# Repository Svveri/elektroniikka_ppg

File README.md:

# elektroniikka_ppg
Elektroniikan sovellusprojektissa suunnittelemme fotopletysmografia periaatteella sydämmensykettä seuraavan laitteen. Tässä repositoriossa säilytämme siihen liittyvät koodit.

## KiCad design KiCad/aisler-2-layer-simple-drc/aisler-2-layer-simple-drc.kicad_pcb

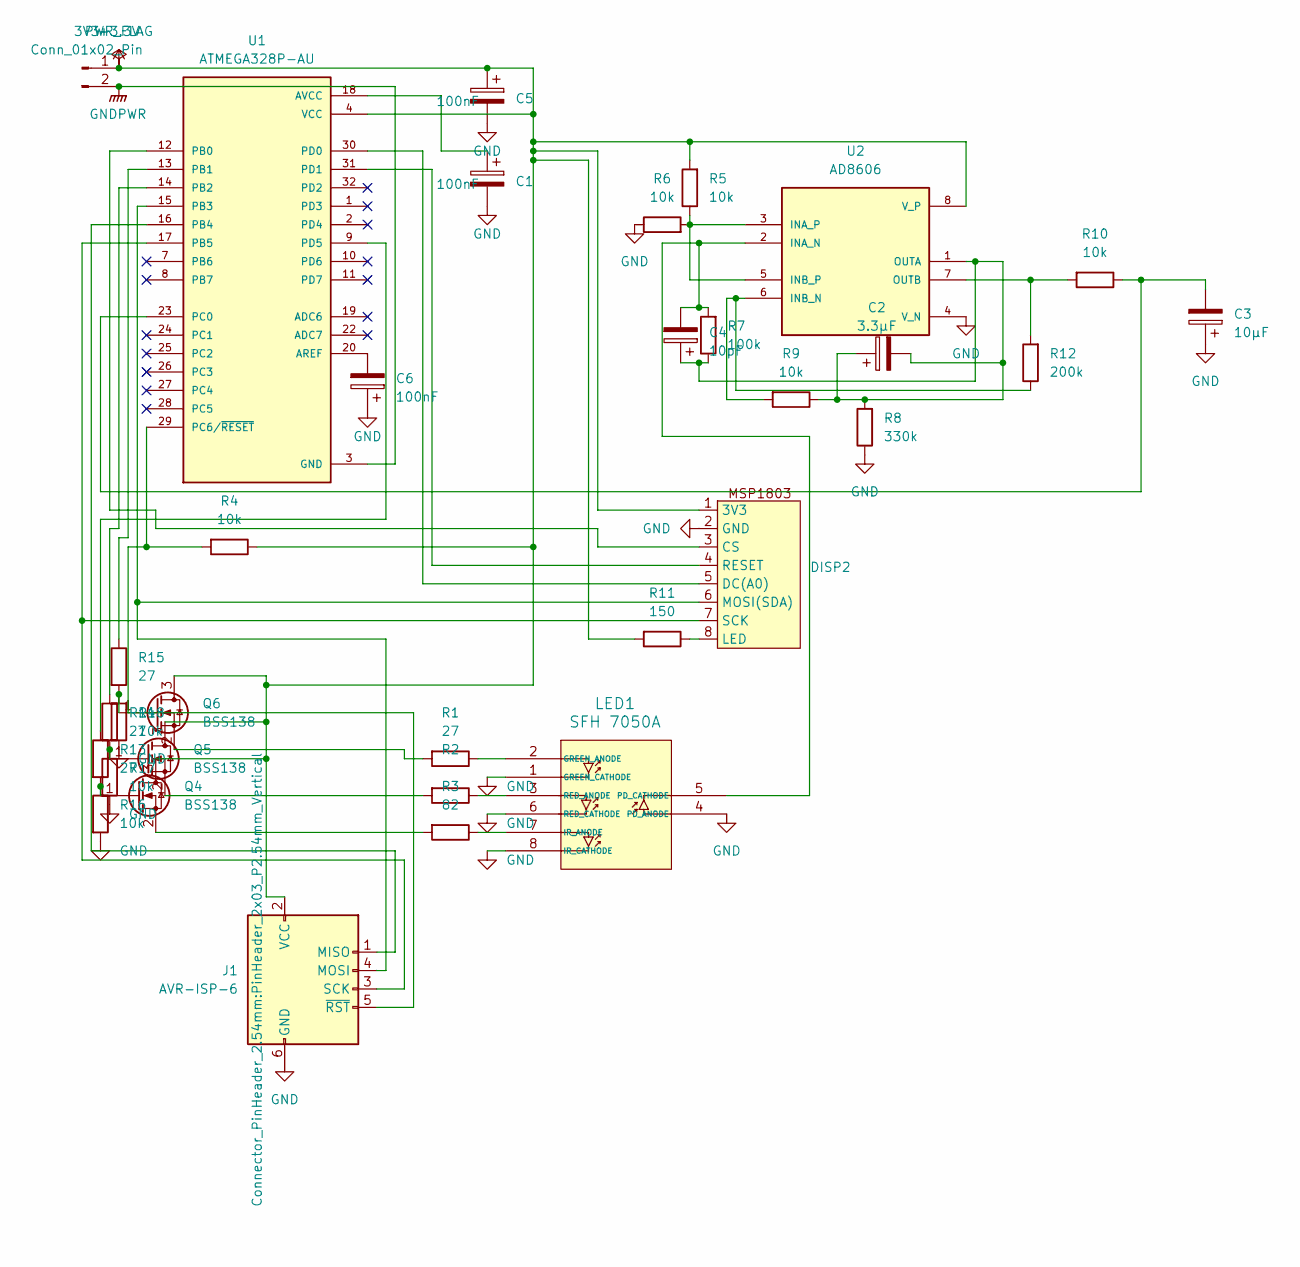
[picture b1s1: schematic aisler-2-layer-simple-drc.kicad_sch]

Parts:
3V3: Conn_01x02_Pin; PinHeader_1x02_P2.54mm_Vertical
C1, C5, C6: 100nF; C_0805_2012Metric
C2: 3.3µF; C_0805_2012Metric
C3: 10µF; C_0805_2012Metric
C4: 10pF; C_0805_2012Metric
DISP2: PinHeader_1x08_P2.54mm_Vertical
J1: AVR-ISP-6; PinHeader_2x03_P2.54mm_Vertical
LED1: SFH 7050A; SFH 7050A_OSM
Q4, Q5, Q6: BSS138; SOT-23
R1, R13, R14, R15: 27; R_0805_2012Metric
R2: 56; R_0805_2012Metric
R3: 82; R_0805_2012Metric
R4, R5, R6, R9, R10, R16, R17, R18: 10k; R_0805_2012Metric
R7: 100k; R_0805_2012Metric
R8: 330k; R_0805_2012Metric
R11: 150; R_0805_2012Metric
R12: 200k; R_0805_2012Metric
U1: ATMEGA328P-AU; TQFP-32_7x7mm_P0.8mm; PARTREV 8271A
U2: AD8606; SOIC-8_3.9x4.9mm_P1.27mm; PARTREV Rev. O

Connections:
+3.3V: 3V3.1, C5.1, DISP2.1 (3V3), J1.2 (VCC), Q4.3 (D), Q5.3 (D), Q6.3 (D), R4.1, R5.2, R11.2, U1.4 (VCC), U1.6 (VCC), U2.8 (V_P)
unnamed: DISP2.3 (CS), U1.12 (PB0)
unnamed: DISP2.5 (DC(A0)), U1.30 (PD0)
unnamed: DISP2.8 (LED), R11.1
unnamed: DISP2.6 (MOSI(SDA)), J1.4 (MOSI), U1.15 (PB3)
unnamed: DISP2.4 (RESET), U1.31 (PD1)
unnamed: DISP2.7 (SCK), J1.3 (SCK), U1.17 (PB5)
unnamed: J1.1 (MISO), U1.16 (PB4)
unnamed: J1.5 (~RST), R4.2, U1.29 (PC6/~RESET)
unnamed: LED1.2 (GREEN_ANODE), R1.1
unnamed: LED1.7 (IR_ANODE), R3.1
unnamed: C4.2, LED1.5 (PD_CATHODE), R7.2, U2.2 (INA_N)
unnamed: LED1.3 (RED_ANODE), R2.1
unnamed: Q4.1 (G), R13.2, R16.1
unnamed: Q4.2 (S), R3.2
unnamed: Q5.1 (G), R14.2, R17.1
unnamed: Q5.2 (S), R2.2
unnamed: Q6.1 (G), R15.2, R18.1
unnamed: Q6.2 (S), R1.2
unnamed: C6.2, U1.20 (AREF)
unnamed: C1.1, U1.18 (AVCC)
unnamed: R15.1, U1.13 (PB1)
unnamed: R14.1, U1.14 (PB2)
unnamed: C3.2, R10.1, U1.23 (PC0)
unnamed: R13.1, U1.9 (PD5)
unnamed: R5.1, R6.2, U2.3 (INA_P), U2.5 (INB_P)
unnamed: R9.2, R12.1, U2.6 (INB_N)
unnamed: C2.1, C2.2, C4.1, R7.1, R8.2, R9.1, U2.1 (OUTA)
unnamed: R10.2, R12.2, U2.7 (OUTB)

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
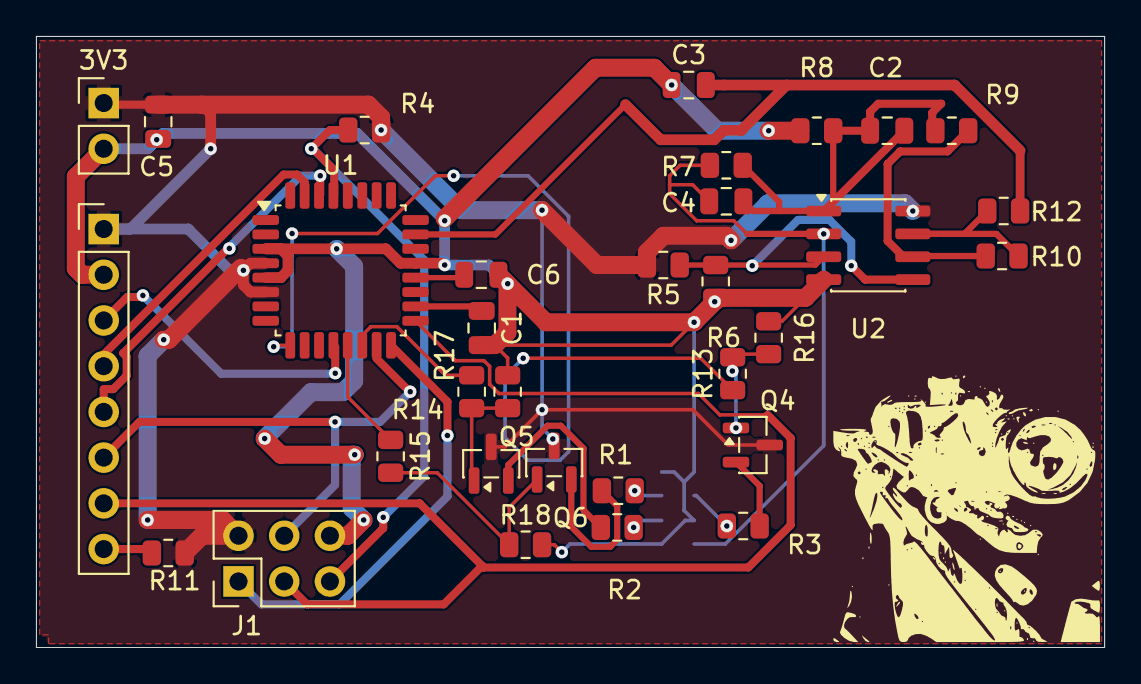
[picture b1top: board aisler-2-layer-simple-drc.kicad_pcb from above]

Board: 2 copper layers, 59.3 x 33.9 mm, 33 parts (1 on the bottom side), 30 nets.

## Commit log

2026-04-01 Poistin .history ja ignoresin sen
2026-04-01 KiCad tiedostot
2026-04-01 Lisätty kooditiedostojen alut kansioon nimeltä koodi. Tiedostoissa ei vielä mitään koodia luotuna tässä vaiheessa
2026-04-02 Validoitu signaalin mittaus DFROBOT_heartrate kirjastolla. Eli A0 pinniin kytkettynä, nappia paineltaessa kykenee mittaamaan signaalin ja printtaamaan sen serial monitorille.
2026-04-07 Added new code (monitor DEMO)
2026-04-08 Lisäsin heart_rate kansioon monitoria varten header ja cpp tiedoston, joilla päästään käsiksi sykkeen luomaan aaltoihin (tällä hetkellä vielä on demo meinaan ei ole sykemittaria. Hyvin kommentoitu ja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
2026-04-09 Yhdistetty RR-intervalli metodia käyttäen toimiva sykkeen mittaus. Tämä koodi toimi hienosti napilla sykettä simuloiden
2026-04-13 Tässä vaiheessa muutettu näytölle menevän muuttujan merkitys, ottaa nyt vastaan napin painalluksen sykkeen eikä simuloida sykettä ohjelmallisesti. Muutettu funktiota ottamaan vastaan muuttuja lastBPM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
2026-04-13 Edelleen toimii samanlailla kuin edellinen, vähän siistitty koodia yms. ei mitään toiminnallista muutosta
2026-04-14 Poistettu turha funktio monitor.cpp, tässä kohtaa koodi edelleen kirjoittaa bpm näytölle, mutta käyrä ei piirry oikein
2026-04-14 Fixed problem with button not showing up on screen, big delay on updated bpm etc.
2026-04-15 Muutettu koodin rr intervalliin liittyvä osa omaksi funktioksi, tässä hetkessä ei koodi vielä toimi kunnolla näytön kanssa
2026-04-16 Siirretty omiin funktioihin asioita ino tiedostosta yms, tässä vaiheessa koodi hajoaa kun syke nousee liian korkeaksi.
2026-04-16 Tässä branchissa testailen vaihtoehtoisia koodeja. Löysin toisen kirjaston nimeltä PulseSensorPlayground, ja sen metodit vaikuttaa toimivan paljon paremmin kuin aikaisemman kirjaston ja itse tekemän 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
2026-04-16 Muutettu koodia radikaalisti, vaihdettu kirjastoa mitä käytetään (PulseSensorPlayground) ja koodi toimii toistaiseksi oikein hyvin. Näytölle piirtyy bpm ja signaalin käyrä oikein hyvin
2026-04-16 Poistettu source.cpp ja source.h toistaiseksi, uuden kirjaston takia ei toistaiseksi niitä tarvita.
2026-04-17 Poistettu (include source.h) koska sitä ei toistaiseksi käytetä
2026-04-17 Edited the heart_rate.ino file in a way it works with atmega328p AU, added the timings for lights etc.
2026-04-27 Muutoksia koodiin monitorissa, näillä alustuksilla ainakin alkoin näytössä näkymään, kun näyttö kiinni pcb:llä
